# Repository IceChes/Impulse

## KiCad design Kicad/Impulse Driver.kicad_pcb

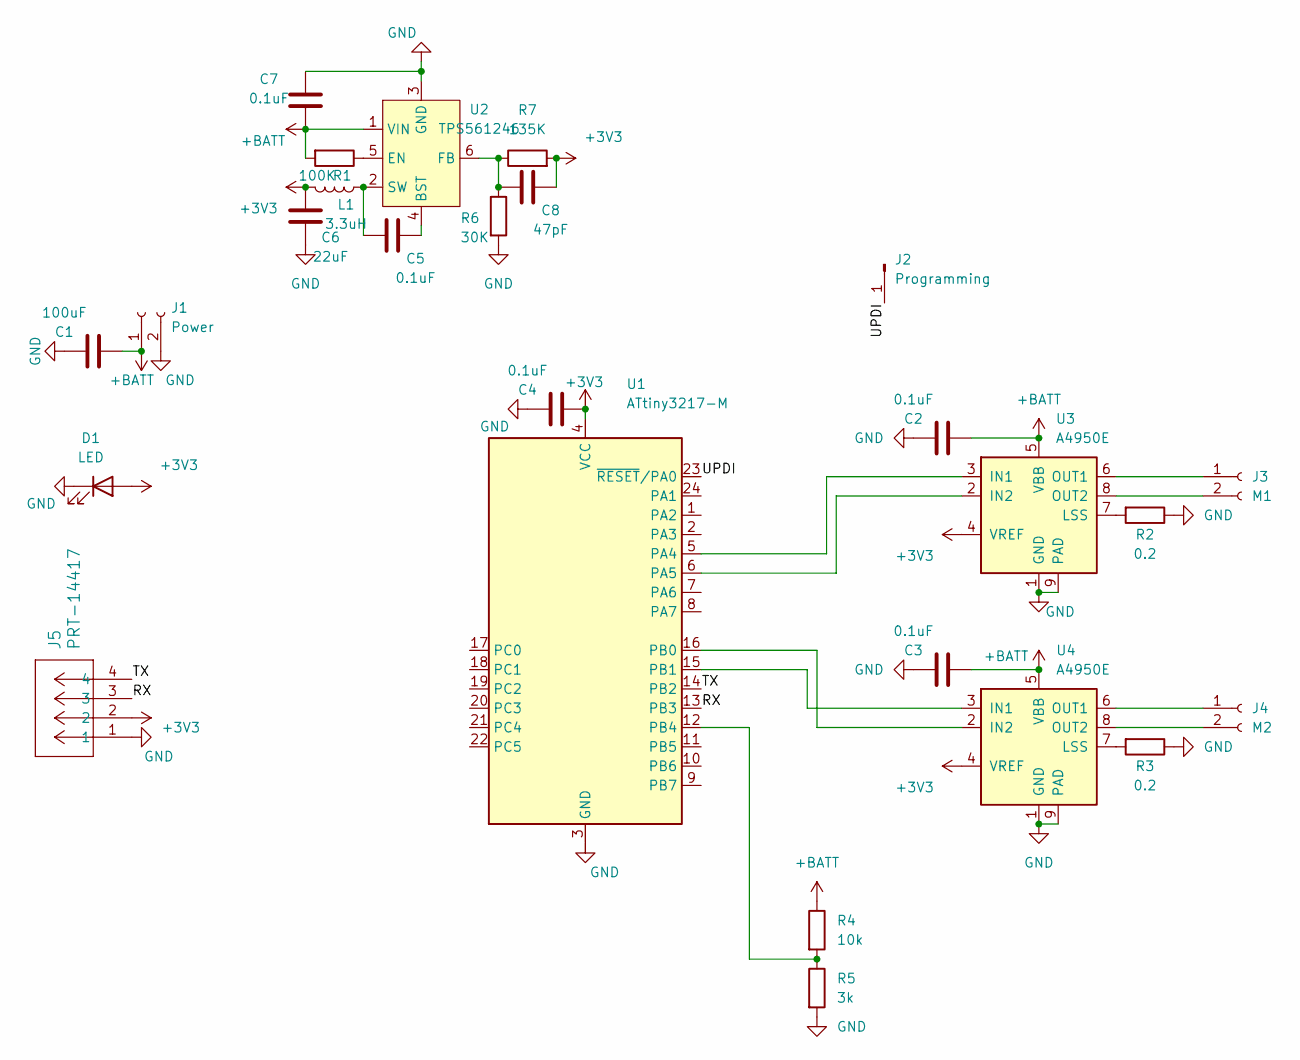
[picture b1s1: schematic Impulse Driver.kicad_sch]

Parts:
C1: 100uF; C_1206_3216Metric
C2, C3, C4, C5, C7: 0.1uF; C_0402_1005Metric
C6: 22uF; C_0402_1005Metric
C8: 47pF; C_0402_1005Metric
D1: LED; LED_0805_2012Metric
J1: Power; PinSocket_1x02_P2.54mm_Vertical
J2: Programming; PinHeader_1x01_P2.54mm_Vertical
J3: M1; PinSocket_1x02_P2.54mm_Vertical
J4: M2; PinSocket_1x02_P2.54mm_Vertical
J5: PRT-14417; QWIIC_SNAPSERIAL
L1: 3.3uH; L_Changjiang_FTC201610S
R1: 100K; R_0402_1005Metric
R2, R3: 0.2; R_0402_1005Metric
R4: 10k; R_0402_1005Metric
R5: 3k; R_0402_1005Metric
R6: 30K; R_0402_1005Metric
R7: 135K; R_0402_1005Metric
U1: ATtiny3217-M; QFN-24-1EP_4x4mm_P0.5mm_EP2.6x2.6mm
U2: TPS561246; SOT-563
U3, U4: A4950E; SOIC-8-1EP_3.9x4.9mm_P1.27mm_EP2.41x3.3mm

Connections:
+3V3: C4.1, C6.1, C8.2, D1.2 (A), J5.2, L1.2, R7.2, U1.4 (VCC), U3.4 (VREF), U4.4 (VREF)
+BATT: C1.1, C2.1, C3.1, C7.2, J1.1, R1.2, R4.1, U2.1 (VIN), U3.5 (VBB), U4.5 (VBB)
/RX: J5.3, U1.13 (PB3)
/TX: J5.4, U1.14 (PB2)
/UPDI: J2.1, U1.23 (~RESET/PA0)
GND: C1.2, C2.2, C3.2, C4.2, C6.2, C7.1, D1.1 (K), J1.2, J5.1, R2.1, R3.1, R5.2, R6.2, U1.3 (GND), U1.25 (GND), U2.3 (GND), U3.1 (GND), U3.9 (PAD), U4.1 (GND), U4.9 (PAD)
unnamed: J3.1, U3.6 (OUT1)
unnamed: J3.2, U3.8 (OUT2)
unnamed: J4.1, U4.6 (OUT1)
unnamed: J4.2, U4.8 (OUT2)
unnamed: U1.5 (PA4), U3.3 (IN1)
unnamed: U1.6 (PA5), U3.2 (IN2)
unnamed: U1.16 (PB0), U4.2 (IN2)
unnamed: U1.15 (PB1), U4.3 (IN1)
unnamed: R4.2, R5.1, U1.12 (PB4)
unnamed: C5.2, U2.4 (BST)
unnamed: R1.1, U2.5 (EN)
unnamed: C8.1, R6.1, R7.1, U2.6 (FB)
unnamed: C5.1, L1.1, U2.2 (SW)
unnamed: R2.2, U3.7 (LSS)
unnamed: R3.2, U4.7 (LSS)

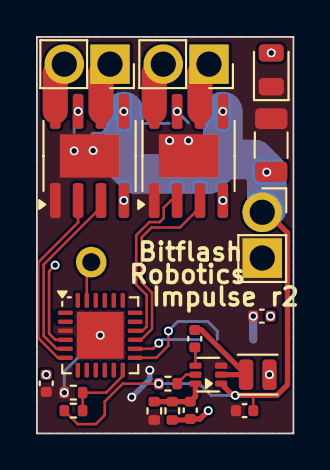
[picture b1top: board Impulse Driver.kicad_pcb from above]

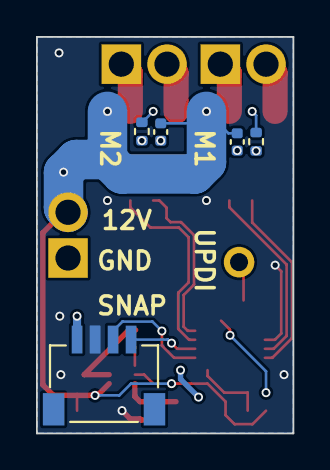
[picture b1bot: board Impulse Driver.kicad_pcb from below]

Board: 2 copper layers, 14.2 x 22.0 mm, 26 parts (5 on the bottom side), 21 nets.

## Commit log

2026-05-27 init
